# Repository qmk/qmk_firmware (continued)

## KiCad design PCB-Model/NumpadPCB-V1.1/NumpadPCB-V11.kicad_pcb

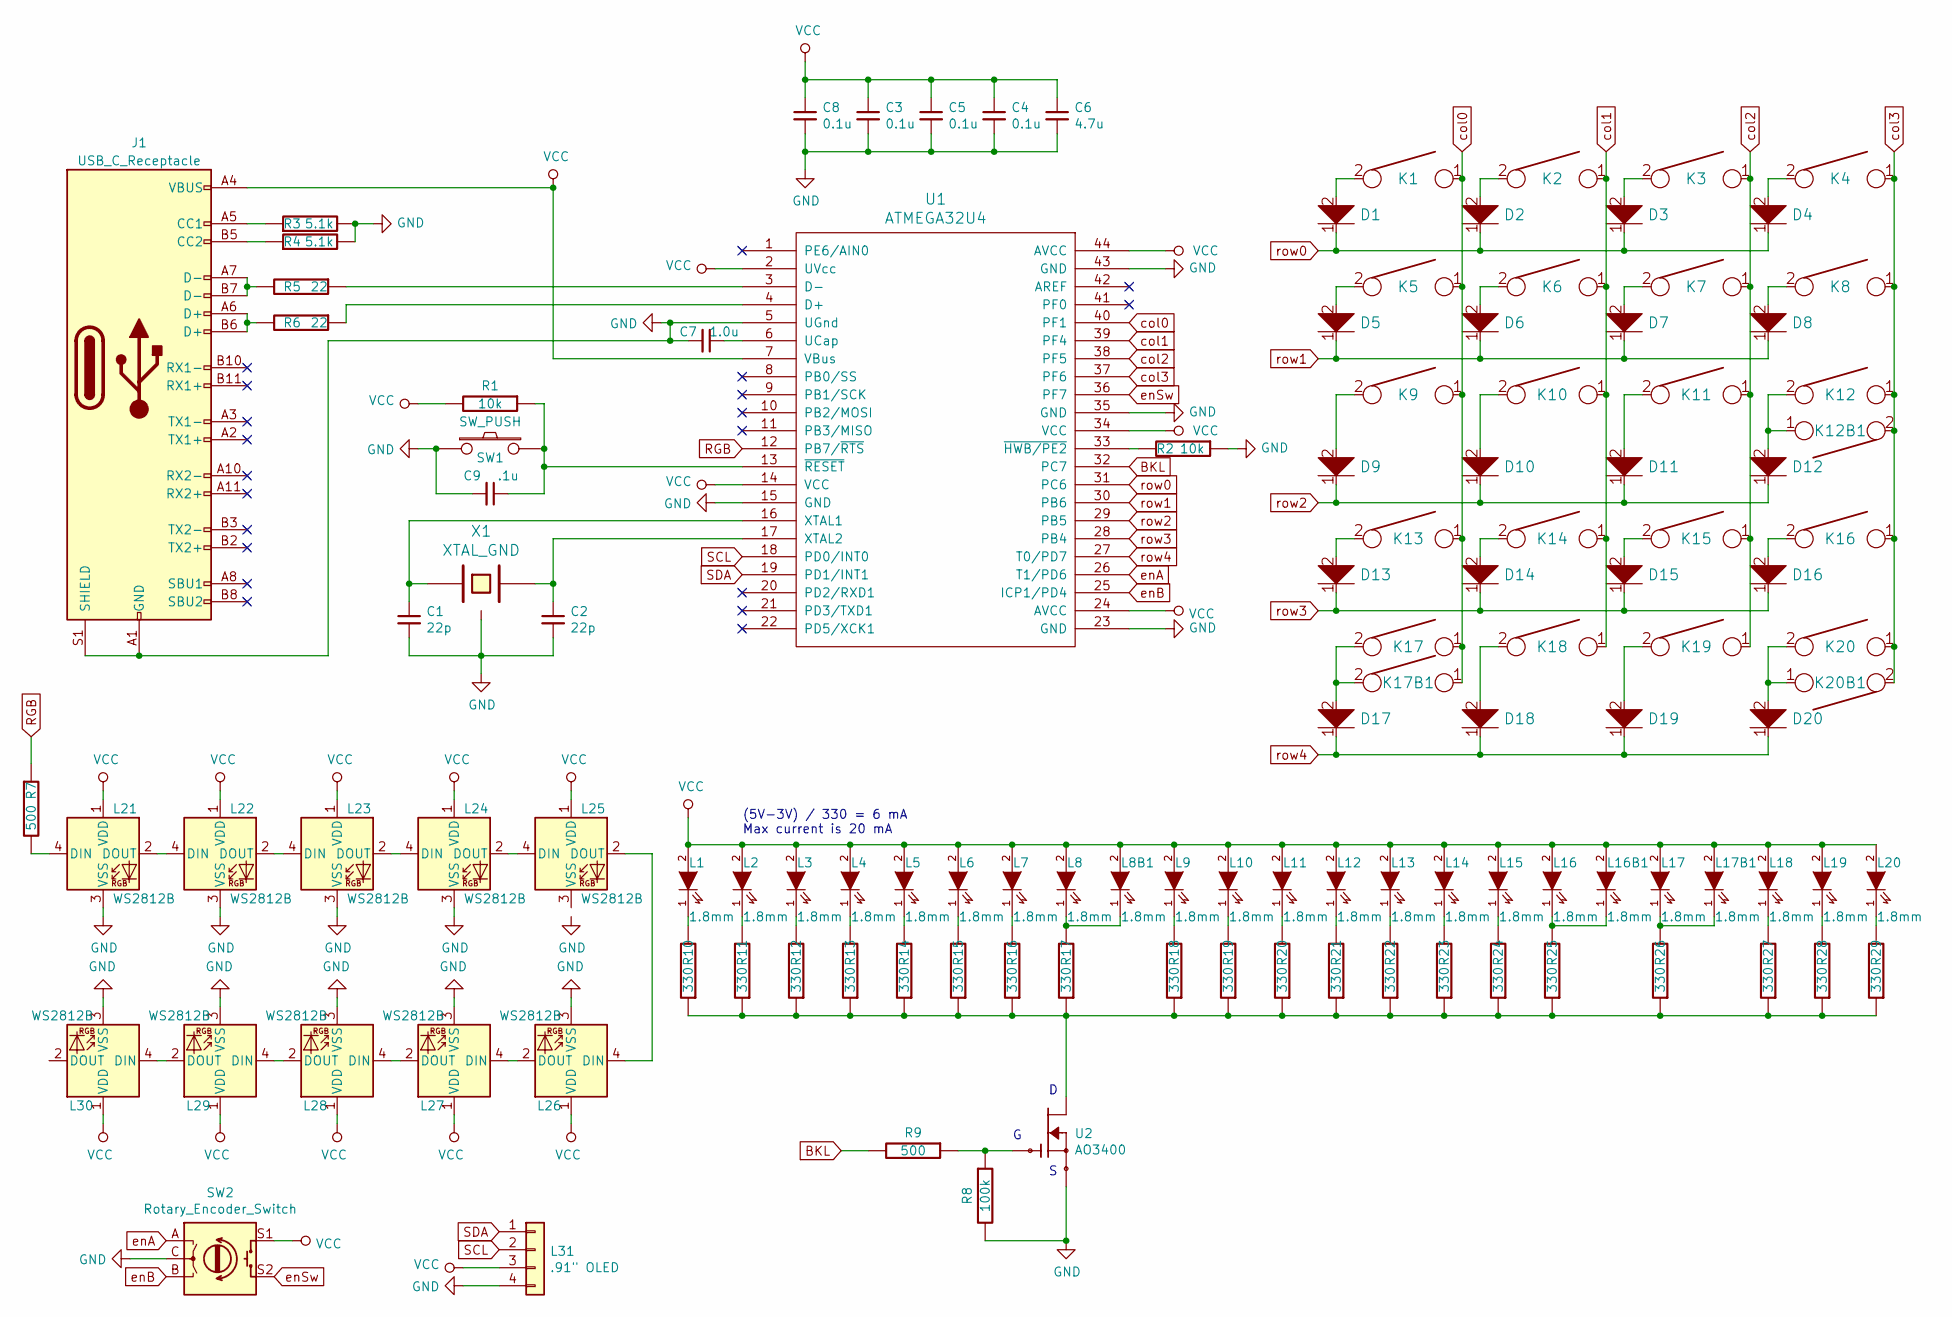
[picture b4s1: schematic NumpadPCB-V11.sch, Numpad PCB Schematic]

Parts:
C1, C2: 22p; C_0805_2012Metric_Pad1.15x1.40mm_HandSolder
C3, C4, C5, C8: 0.1u; C_0805_2012Metric_Pad1.15x1.40mm_HandSolder
C6: 4.7u; C_0805_2012Metric_Pad1.15x1.40mm_HandSolder
C7: 1.0u; C_0805_2012Metric_Pad1.15x1.40mm_HandSolder
C9: .1u; C_0805_2012Metric_Pad1.15x1.40mm_HandSolder
D1, D2, D3, D4, D5, D6, D7, D8, D9, D10, D11, D12, D13, D14, D15, D16, D17, D18, D19, D20: D; D_SOD123_axial
J1: USB_C_Receptacle; USB_C_Receptacle_Amphenol_12401548E4-2A
K1, K2, K3, K4, K5, K6, K7, K8, K9, K10, K11, K12, K13, K14, K15, K16, K17, K18, K19, K20: KEYSW; SW_Cherry_MX_1.00u_Plate
K12B1, K20B1: KEYSW; SW_Cherry_MX_2.00u_Vertical_Plate
K17B1: KEYSW; SW_Cherry_MX_2.00u_Plate
L1, L2, L3, L4, L5, L6, L7, L8, L8B1, L9, L10, L11, L12, L13, L14, L15, L16, L16B1, L17, L17B1, L18, L19, L20: 1.8mm; LED_TH
L21, L22, L23, L24, L25, L26, L27, L28, L29, L30: WS2812B; LED_WS2812B_PLCC4_5.0x5.0mm_P3.2mm
L31: .91\" OLED; PinSocket_1x04_P2.54mm_Vertical
R1, R2: 10k; R_0805_2012Metric_Pad1.15x1.40mm_HandSolder
R3, R4: 5.1k; R_0805_2012Metric_Pad1.15x1.40mm_HandSolder
R5, R6: 22; R_0805_2012Metric_Pad1.15x1.40mm_HandSolder
R7, R9: 500; R_0805_2012Metric_Pad1.15x1.40mm_HandSolder
R8: 100k; R_0805_2012Metric_Pad1.15x1.40mm_HandSolder
R10, R11, R12, R13, R14, R15, R16, R17, R18, R19, R20, R21, R22, R23, R24, R25, R26, R27, R28, R29: 330; R_0805_2012Metric_Pad1.15x1.40mm_HandSolder
SW1: SW_PUSH; SW_SPST_TL3342
SW2: Rotary_Encoder_Switch; RotaryEncoder_Alps_EC12E-Switch_Vertical_H20mm
U1: ATMEGA32U4; TQFP-44-1EP_10x10mm_P0.8mm_EP4.5x4.5mm
U2: AO3400; SOT23
X1: XTAL_GND; FA-238

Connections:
BKL: R9.2, U1.32 (PC7)
GND: C1.2, C2.2, C3.2, C4.2, C5.2, C6.2, C7.2, C8.2, C9.2, J1.A1 (GND), J1.A12 (GND), J1.B1 (GND), J1.B12 (GND), J1.S1 (SHIELD), L21.3 (VSS), L22.3 (VSS), L23.3 (VSS), L24.3 (VSS), L26.3 (VSS), L27.3 (VSS), L28.3 (VSS), L29.3 (VSS), L30.3 (VSS), L31.4, R2.1, R3.2, R4.2, R8.2, SW1.1, SW2.C, U1.5 (UGnd), U1.15 (GND), U1.23 (GND), U1.35 (GND), U1.43 (GND), U2.2 (S), X1.3
unnamed: C1.1, U1.16 (XTAL1), X1.1
unnamed: C2.1, U1.17 (XTAL2), X1.2
unnamed: C7.1, U1.6 (UCap)
unnamed: C9.1, R1.1, SW1.2, U1.13 (~RESET)
unnamed: D1.2, K1.2
unnamed: D2.2, K2.2
unnamed: D3.2, K3.2
unnamed: D4.2, K4.2
unnamed: D5.2, K5.2
unnamed: D6.2, K6.2
unnamed: D7.2, K7.2
unnamed: D8.2, K8.2
unnamed: D9.2, K9.2
unnamed: D10.2, K10.2
unnamed: D11.2, K11.2
unnamed: D12.2, K12.2, K12B1.1
unnamed: D13.2, K13.2
unnamed: D14.2, K14.2
unnamed: D15.2, K15.2
unnamed: D16.2, K16.2
unnamed: D17.2, K17.2, K17B1.2
unnamed: D18.2, K18.2
unnamed: D19.2, K19.2
unnamed: D20.2, K20.2, K20B1.1
unnamed: J1.A5 (CC1), R3.1
unnamed: J1.A6 (D+), J1.B6 (D+), R6.2
unnamed: J1.A7 (D-), J1.B7 (D-), R5.2
unnamed: J1.B5 (CC2), R4.1
unnamed: L1.1 (K), R10.2
unnamed: L2.1 (K), R11.2
unnamed: L3.1 (K), R12.2
unnamed: L4.1 (K), R13.2
unnamed: L5.1 (K), R14.2
unnamed: L6.1 (K), R15.2
unnamed: L7.1 (K), R16.2
unnamed: L8.1 (K), L8B1.1 (K), R17.2
unnamed: L9.1 (K), R18.2
unnamed: L10.1 (K), R19.2
unnamed: L11.1 (K), R20.2
unnamed: L12.1 (K), R21.2
unnamed: L13.1 (K), R22.2
unnamed: L14.1 (K), R23.2
unnamed: L15.1 (K), R24.2
unnamed: L16.1 (K), L16B1.1 (K), R25.2
unnamed: L17.1 (K), L17B1.1 (K), R26.2
unnamed: L18.1 (K), R27.2
unnamed: L19.1 (K), R28.2
unnamed: L20.1 (K), R29.2
unnamed: L21.2 (DOUT), L22.4 (DIN)
unnamed: L21.4 (DIN), R7.2
unnamed: L22.2 (DOUT), L23.4 (DIN)
unnamed: L23.2 (DOUT), L24.4 (DIN)
unnamed: L24.2 (DOUT), L25.4 (DIN)
unnamed: L25.2 (DOUT), L26.4 (DIN)
unnamed: L26.2 (DOUT), L27.4 (DIN)
unnamed: L27.2 (DOUT), L28.4 (DIN)
unnamed: L28.2 (DOUT), L29.4 (DIN)
unnamed: L29.2 (DOUT), L30.4 (DIN)
unnamed: R2.2, U1.33 (~HWB/PE2)
unnamed: R5.1, U1.3 (D-)
unnamed: R6.1, U1.4 (D+)
unnamed: R8.1, R9.1, U2.1 (G)
unnamed: R10.1, R11.1, R12.1, R13.1, R14.1, R15.1, R16.1, R17.1, R18.1, R19.1, R20.1, R21.1, R22.1, R23.1, R24.1, R25.1, R26.1, R27.1, R28.1, R29.1, U2.3 (D)
RGB: R7.1, U1.12 (PB7/~RTS)
SCL: L31.2, U1.18 (PD0/INT0)
SDA: L31.1, U1.19 (PD1/INT1)
VCC: C3.1, C4.1, C5.1, C6.1, C8.1, J1.A4 (VBUS), J1.A9 (VBUS), J1.B4 (VBUS), J1.B9 (VBUS), L1.2 (A), L2.2 (A), L3.2 (A), L4.2 (A), L5.2 (A), L6.2 (A), L7.2 (A), L8.2 (A), L8B1.2 (A), L9.2 (A), L10.2 (A), L11.2 (A), L12.2 (A), L13.2 (A), L14.2 (A), L15.2 (A), L16.2 (A), L16B1.2 (A), L17.2 (A), L17B1.2 (A), L18.2 (A), L19.2 (A), L20.2 (A), L21.1 (VDD), L22.1 (VDD), L23.1 (VDD), L24.1 (VDD), L25.1 (VDD), L26.1 (VDD), L27.1 (VDD), L28.1 (VDD), L29.1 (VDD), L30.1 (VDD), L31.3, R1.2, SW2.S1, U1.2 (UVcc), U1.7 (VBus), U1.14 (VCC), U1.24 (AVCC), U1.34 (VCC), U1.44 (AVCC)
col0: K1.1, K5.1, K9.1, K13.1, K17.1, K17B1.1, U1.40 (PF1)
col1: K2.1, K6.1, K10.1, K14.1, K18.1, U1.39 (PF4)
col2: K3.1, K7.1, K11.1, K15.1, K19.1, U1.38 (PF5)
col3: K4.1, K8.1, K12.1, K12B1.2, K16.1, K20.1, K20B1.2, U1.37 (PF6)
enA: SW2.A, U1.26 (T1/PD6)
enB: SW2.B, U1.25 (ICP1/PD4)
enSw: SW2.S2, U1.36 (PF7)
row0: D1.1, D2.1, D3.1, D4.1, U1.31 (PC6)
row1: D5.1, D6.1, D7.1, D8.1, U1.30 (PB6)
row2: D9.1, D10.1, D11.1, D12.1, U1.29 (PB5)
row3: D13.1, D14.1, D15.1, D16.1, U1.28 (PB4)
row4: D17.1, D18.1, D19.1, D20.1, U1.27 (T0/PD7)

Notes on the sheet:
(5V-3V) / 330 = 6 mA Max current is 20 mA

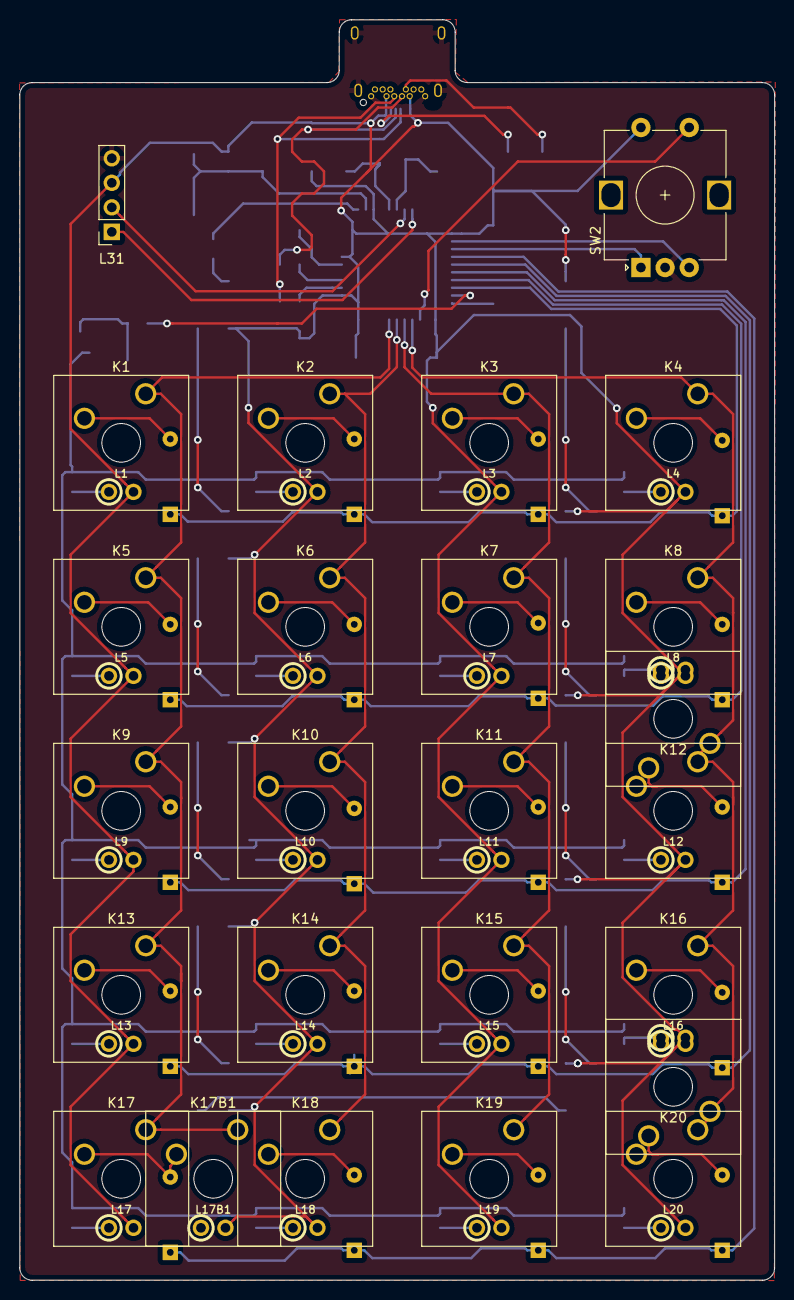
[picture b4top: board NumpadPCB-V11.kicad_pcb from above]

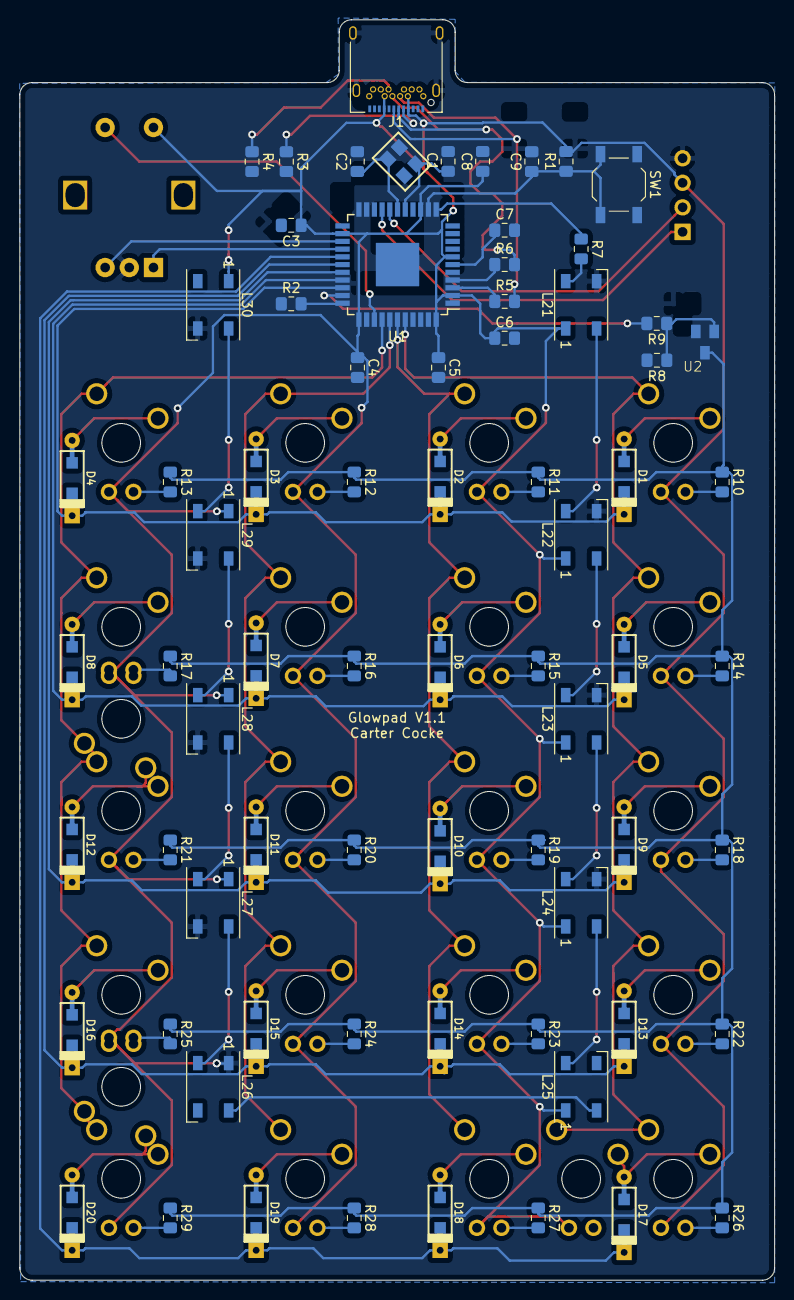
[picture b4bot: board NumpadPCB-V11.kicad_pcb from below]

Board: 2 copper layers, 78.2 x 130.5 mm, 121 parts (73 on the bottom side), 81 nets.
